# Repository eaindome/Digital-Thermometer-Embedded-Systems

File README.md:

# Digital-Thermometer-Embedded-Systems
Designing a digital thermometer using PIC microcontroller and DB1820 temperature sensor

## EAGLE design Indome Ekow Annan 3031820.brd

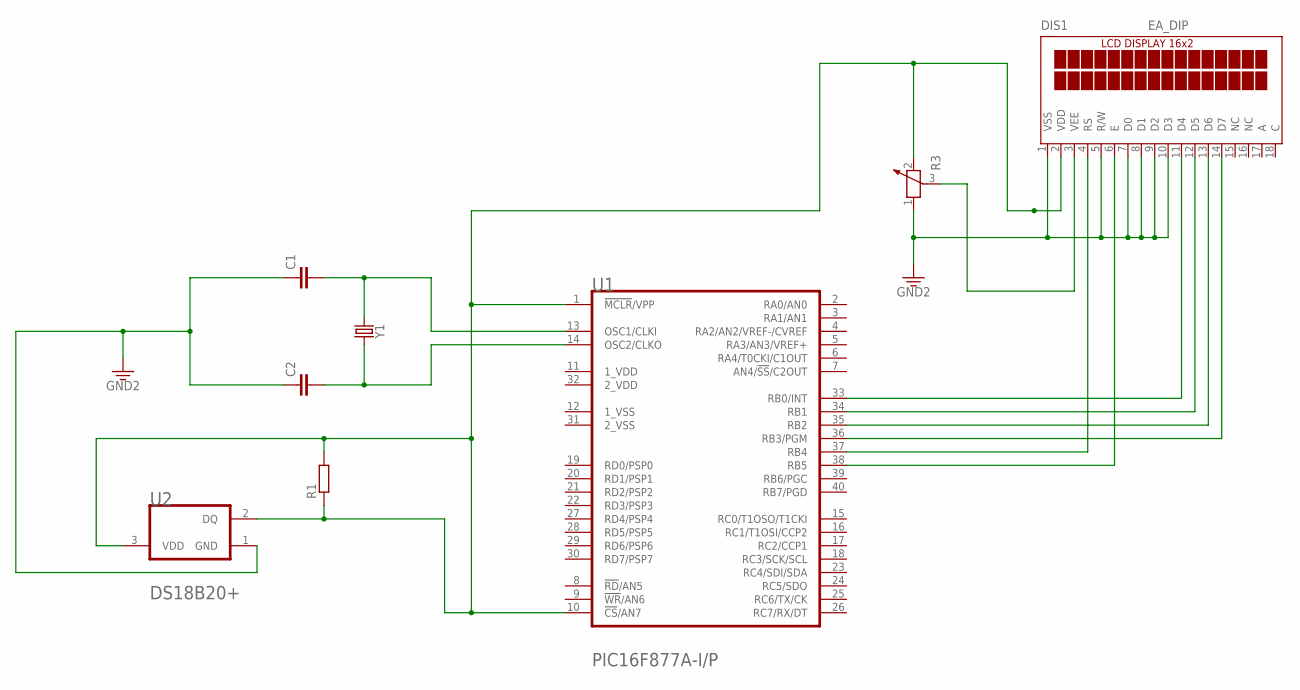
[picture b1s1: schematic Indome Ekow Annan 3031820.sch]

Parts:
C1, C2: C2,5-3; C2.5-3
DIS1: EA_DIP
R1: R-EU_0204/2V; 0204V
R3: POTENTIOMETER_PT-10; PT-10
U1: MICROCHIP_PIC16F877A-I-PMICROCHIP_PIC16F877A-I-P_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; MICROCHIP_PIC16F877A-I-P_0
U2: MAXIM_DS18B20+MAXIM_DS18B20+_0_0; MAXIM_DS18B20+_0
Y1: CRYSTALPTH-2X6; CRYSTAL-PTH-2X6-CYL

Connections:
1_VDD: U1.11 (1_VDD)
1_VSS: U1.12 (1_VSS)
2_VDD: U1.32 (2_VDD)
2_VSS: U1.31 (2_VSS)
3.3V: C1.1, C2.1, DIS1.1 (VSS), DIS1.5 (R/W), DIS1.7 (D0), DIS1.8 (D1), DIS1.9 (D2), DIS1.10 (D3), R3.1, U2.1 (GND)
unnamed: DIS1.2 (VDD), R1.1, R1.2, R3.2, U1.1 (!MCLR!/VPP), U1.10 (!CS!/AN7), U2.2 (DQ), U2.3 (VDD)
unnamed: DIS1.3 (VEE), R3.3
unnamed: DIS1.6 (E), U1.38 (RB5)
unnamed: C1.2, U1.13 (OSC1/CLKI), Y1.1
unnamed: C2.2, U1.14 (OSC2/CLKO), Y1.2
unnamed: DIS1.4 (RS), U1.37 (RB4)
unnamed: DIS1.11 (D4), U1.33 (RB0/INT)
unnamed: DIS1.12 (D5), U1.34 (RB1)
unnamed: DIS1.13 (D6), U1.35 (RB2)
unnamed: DIS1.14 (D7), U1.36 (RB3/PGM)

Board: 2 copper layers, 8 parts (0 on the bottom side), 11 nets, no tracks yet.

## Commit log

2023-07-19 Add files via upload
    Uploading files

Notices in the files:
parts and their libraries:
SparkFun-Clocks: Licensing: Creative Commons ShareAlike 4.0 International - https://creativecommons.org/licenses/by-sa/4.0
